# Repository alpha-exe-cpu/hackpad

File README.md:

# 9-Key XIAO RP2040 Hackpad

So I've made a compact and customizable 9-key macro pad powered by the **Seeed Studio XIAO RP2040**, running **KMK Firmware**.  
The keys are mapped to **F13–F21** and I added **0.91" SSD1306 I²C OLED display** which will show real-time **clock + date**.

---

## Hardware Overview

### **Components**
- Seeed Studio XIAO RP2040  
- 9× mechanical switches  
- 0.91" SSD1306 OLED (128×32, I²C)

---

## Wiring

### **OLED Connection**

| XIAO RP2040 Pin | OLED Pin |
|-----------------|----------|
| GND             | GND      |
| 3V3             | VCC      |
| GPIO26          | SCL      |
| GPIO27          | SDA      |

---

### **Switch Mapping**  
Each switch has one side connected to **GND** and the other to a **GPIO pin**.

| Switch | XIAO GPIO | HID Key |
|--------|-----------|---------|
| SW1    | GP1       | F19     |
| SW2    | GP2       | F20     |
| SW3    | GP4       | F21     |
| SW4    | GP3       | F16     |
| SW5    | GP0       | F17     |
| SW6    | GP7       | F18     |
| SW7    | GP6       | F13     |
| SW8    | GP29      | F14     |
| SW9    | GP28      | F15     |

---

## Schematic

---

## PCB

---
## 3D Render (All Components)

---

## 3D Render (without PCB)

---
## 3D Render (Assembled)

---

## Firmware

The hackpad runs on **KMK Firmware** which is a lightweight Python-based keyboard firmware stored directly on the device’s flash.

---

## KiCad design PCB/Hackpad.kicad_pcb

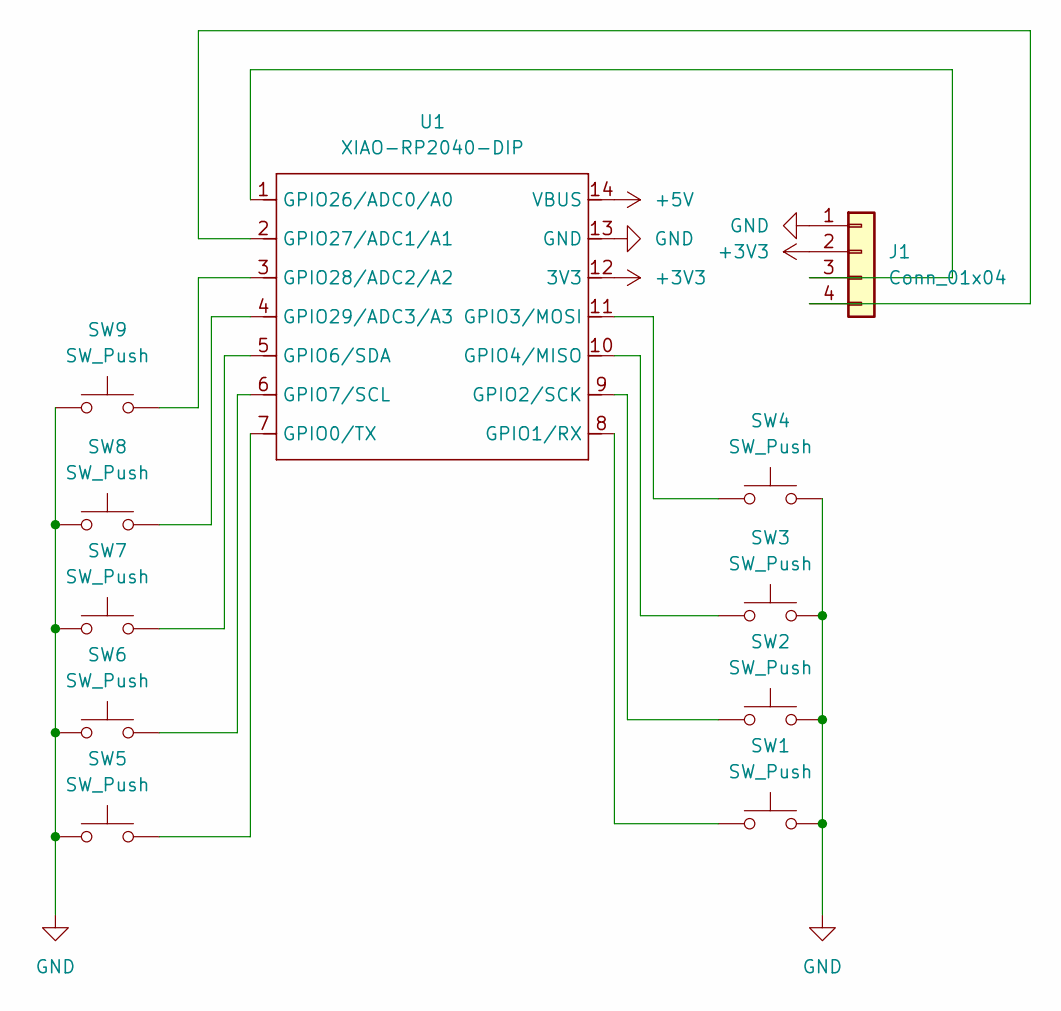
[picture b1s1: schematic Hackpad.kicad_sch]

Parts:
J1: Conn_01x04; SSD1306-0.91-OLED-4pin-128x32
SW1, SW2, SW3, SW4, SW5, SW6, SW7, SW8, SW9: SW_Push; SW_Cherry_MX_1.00u_PCB
U1: XIAO-RP2040-DIP

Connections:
+3V3: J1.2, U1.12 (3V3)
+5V: U1.14 (VBUS)
GND: J1.1, SW1.1, SW2.2, SW3.2, SW4.2, SW5.1, SW6.1, SW7.1, SW8.1, SW9.1, U1.13 (GND)
unnamed: J1.3, U1.1 (GPIO26/ADC0/A0)
unnamed: J1.4, U1.2 (GPIO27/ADC1/A1)
unnamed: SW5.2, U1.7 (GPIO0/TX)
unnamed: SW1.2, U1.8 (GPIO1/RX)
unnamed: SW2.1, U1.9 (GPIO2/SCK)
unnamed: SW4.1, U1.11 (GPIO3/MOSI)
unnamed: SW3.1, U1.10 (GPIO4/MISO)
unnamed: SW7.2, U1.5 (GPIO6/SDA)
unnamed: SW6.2, U1.6 (GPIO7/SCL)
unnamed: SW9.2, U1.3 (GPIO28/ADC2/A2)
unnamed: SW8.2, U1.4 (GPIO29/ADC3/A3)

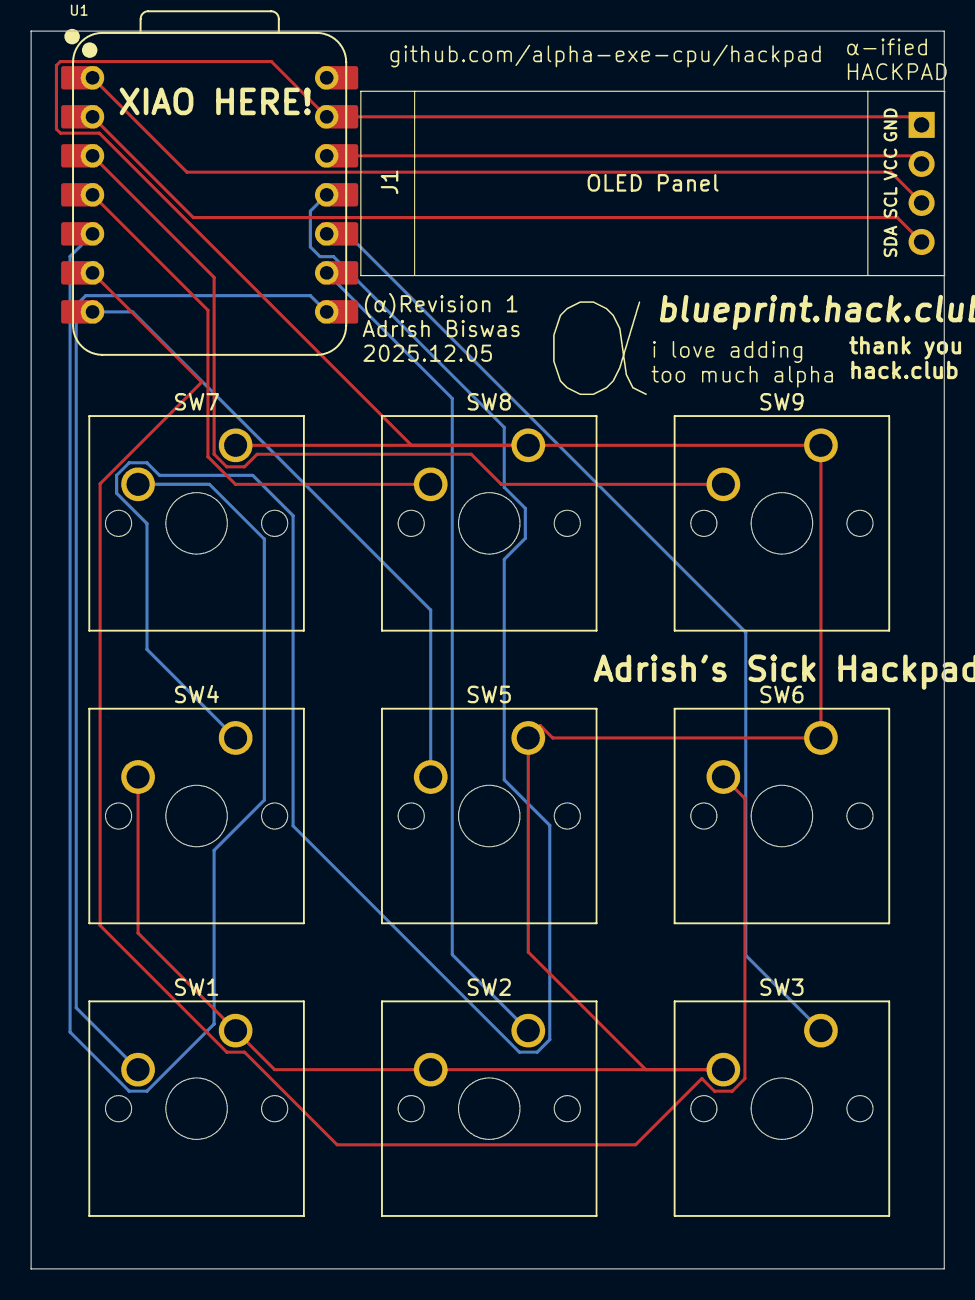
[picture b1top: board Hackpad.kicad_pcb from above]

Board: 2 copper layers, 59.4 x 80.6 mm, 11 parts (0 on the bottom side), 13 nets.

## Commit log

2025-12-06 Create main
2025-12-06 KiCad Files...
2025-12-06 All Step Files...
2025-12-06 Create All STEP Files...
2025-12-06 Create d
2025-12-06 Firmware Files...
2025-12-06 Firmware on the root as instructed by the guide
2025-12-06 Create Repository
2025-12-06 code.py
